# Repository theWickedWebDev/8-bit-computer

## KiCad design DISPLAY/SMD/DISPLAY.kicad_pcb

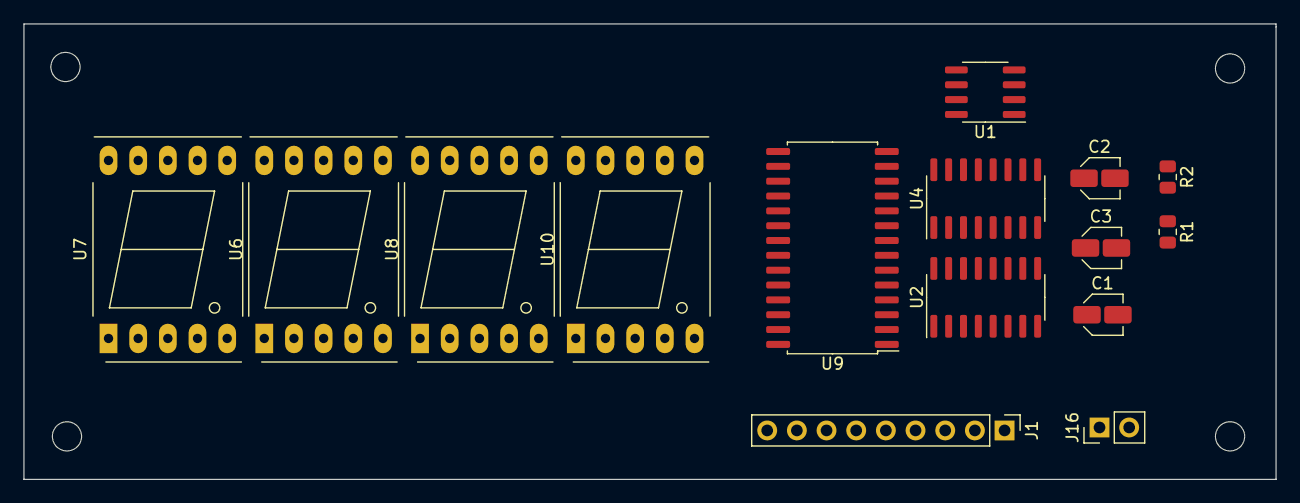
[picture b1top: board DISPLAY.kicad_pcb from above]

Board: 2 copper layers, 107.2 x 39.0 mm, 15 parts (0 on the bottom side), 28 nets, no tracks yet.

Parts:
C1, C3: CP; C_Elec_3x5.4
C2: C; C_Elec_3x5.4
J1: Conn_01x09; PinHeader_1x09_P2.54mm_Vertical
J16: Conn_01x04; PinHeader_1x02_P2.54mm_Vertical
R1, R2: R_US; R_0805_2012Metric
U1: LM555CM_NOPB; SOIC-8_3.9x4.9mm_P1.27mm
U2: 74LS76; SOIC-16_3.9x9.9mm_P1.27mm
U4: 74LS139; SOIC-16_3.9x9.9mm_P1.27mm
U6, U7, U8, U10: HDSP-7503; 7SegmentLED_LTS6760_LTS6780
U9: AT28C256; SOIC-28W_7.5x17.9mm_P1.27mm

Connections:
/A: U6.10, U7.10, U8.10, U9.11, U10.10
/B: U6.9, U7.9, U8.9, U9.12, U10.9
/C: U6.8, U7.8, U8.8, U9.13, U10.8
/CLOCK_DISPLAY: U1.3, U2.12
/D: U6.5, U7.5, U8.5, U9.15, U10.5
/DP: U6.7, U7.7, U8.7, U10.7
/E: U6.4, U7.4, U8.4, U9.16, U10.4
/F: U6.2, U7.2, U8.2, U9.17, U10.2
/G: U6.3, U7.3, U8.3, U9.18, U10.3
GND: C1.1, C2.2, C3.2, J16.2, U1.1, U2.8, U4.3, U4.4, U4.5, U4.8, U9.14, U9.20, U9.22
unnamed: C1.2, R1.2, U1.2, U1.6
unnamed: C2.1, U1.5
unnamed: J1.1, U9.10
unnamed: J1.2, U9.9
unnamed: J1.3, U9.8
unnamed: J1.4, U9.7
unnamed: J1.5, U9.6
unnamed: J1.6, U9.5
unnamed: J1.7, U9.4
unnamed: J1.8, U9.3
unnamed: J1.9, U9.25
unnamed: R1.1, R2.1, U1.7
unnamed: U2.4, U2.9, U4.1, U9.24
unnamed: U4.12, U6.1, U6.6
unnamed: U4.13, U7.1, U7.6
unnamed: U4.14, U8.1, U8.6
unnamed: U4.15, U10.1, U10.6
VCC: C3.1, J16.1, R2.2, U1.8, U2.1, U2.2, U2.3, U2.5, U2.6, U2.11, U2.13, U2.14, U2.15, U2.16, U4.2, U4.6, U4.16, U9.21, U9.27, U9.28

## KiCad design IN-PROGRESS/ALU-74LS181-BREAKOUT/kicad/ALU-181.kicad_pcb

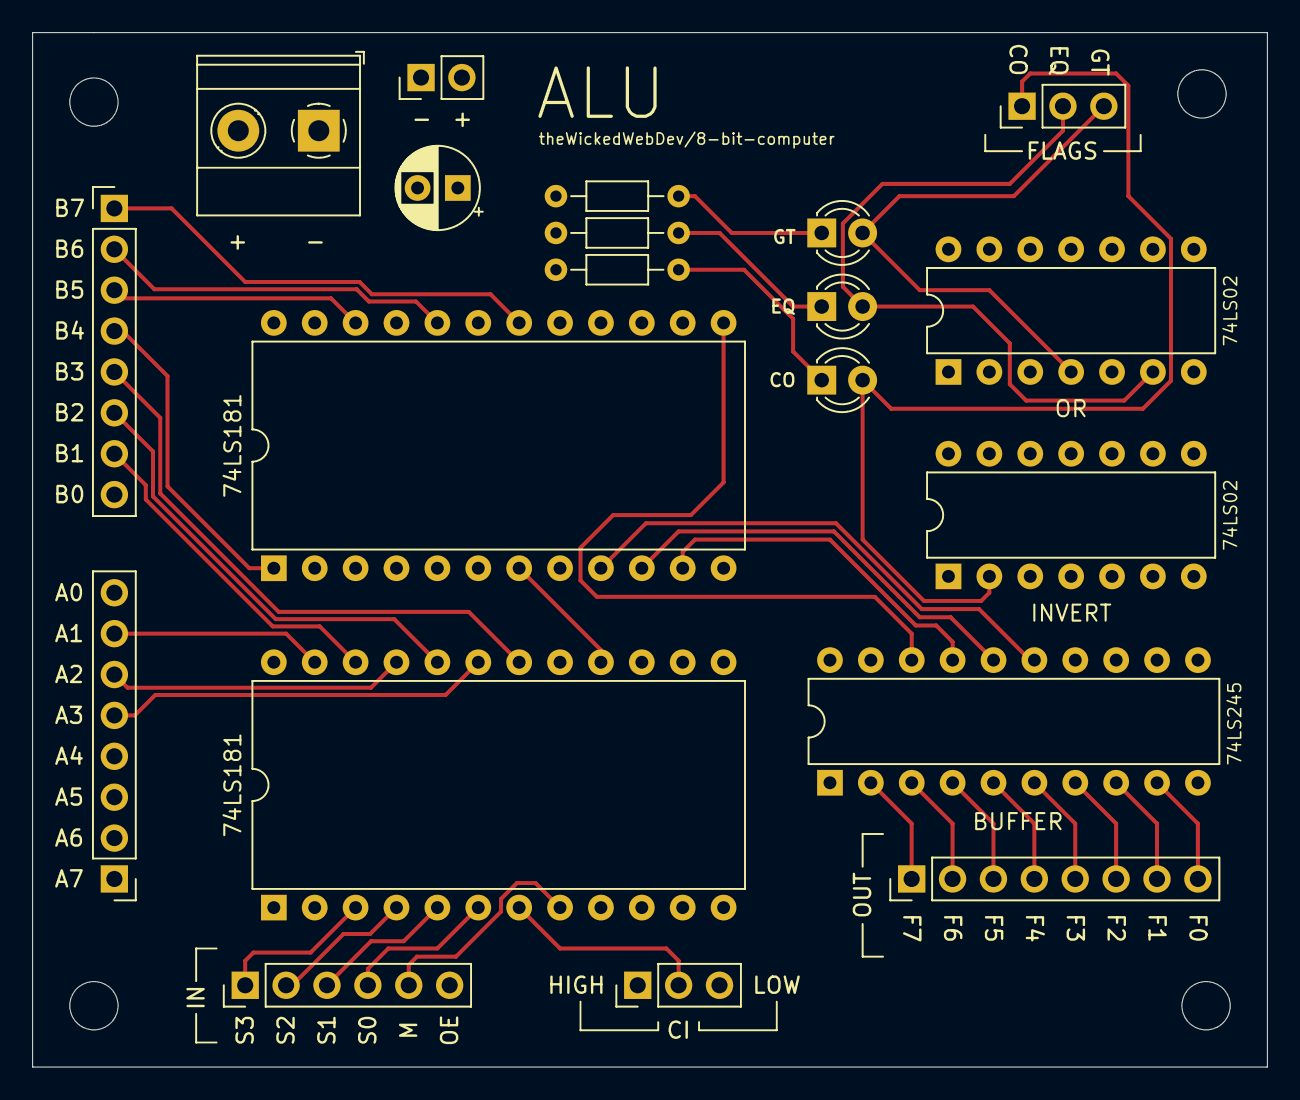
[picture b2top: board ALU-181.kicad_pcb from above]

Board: 4 copper layers, 76.7 x 64.3 mm, 20 parts (0 on the bottom side), 49 nets.

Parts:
C1: CP1_Small; CP_Radial_D5.0mm_P2.50mm
D1, D3, D4: LED; LED_D3.0mm
J1: Conn_01x02; PinHeader_1x02_P2.54mm_Vertical
J2: Screw_Terminal_01x02; TerminalBlock_Phoenix_MKDS-1,5-2_1x02_P5.00mm_Horizontal
J3, J4, J5: Conn_01x08; PinHeader_1x08_P2.54mm_Vertical
J6: Conn_01x06; PinHeader_1x06_P2.54mm_Vertical
J7, J8: Conn_01x03; PinHeader_1x03_P2.54mm_Vertical
R1, R3, R4: R_Small_US; R_Axial_DIN0204_L3.6mm_D1.6mm_P7.62mm_Horizontal
U1, U2: 74LS181; DIP-24_W15.24mm
U3: 74LS02; DIP-14_W7.62mm
U4: 74LS04; DIP-14_W7.62mm
U5: 74LS245; DIP-20_W7.62mm

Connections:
/A0: J4.8, U2.2
/A1: J4.7, U2.23
/A2: J4.6, U2.21
/A3: J4.5, U2.19
/A4: J4.4, U1.2
/A5: J4.3, U1.23
/A6: J4.2, U1.21
/A7: J4.1, U1.19
/A==B: D3.2, J7.2, U1.14, U2.14, U3.6
/A>B: D1.2, J7.3, U3.4
/B0: J5.8, U2.1
/B1: J5.7, U2.22
/B2: J5.6, U2.20
/B3: J5.5, U2.18
/B4: J5.4, U1.1
/B5: J5.3, U1.22
/B6: J5.2, U1.20
/B7: J5.1, U1.18
/CARRY: D4.2, J7.1, U4.2
/F0: J3.8, U5.9
/F1: J3.7, U5.8
/F2: J3.6, U5.7
/F3: J3.5, U5.6
/F4: J3.4, U5.5
/F5: J3.3, U5.4
/F6: J3.2, U5.3
/F7: J3.1, U5.2
/MODE: J6.5, U1.8, U2.8
/OE: J6.6, U5.19
/S0: J6.4, U1.6, U2.6
/S1: J6.3, U1.5, U2.5
/S2: J6.2, U1.4, U2.4
/S3: J6.1, U1.3, U2.3
GND: C1.2, J1.1, J2.1, J8.3, R1.2, R3.2, R4.2, U1.12, U2.12, U3.7, U4.7, U5.1, U5.10
unnamed: D1.1, R1.1
unnamed: D3.1, R3.1
unnamed: D4.1, R4.1
unnamed: J8.2, U2.7
unnamed: U1.7, U2.16
unnamed: U1.9, U5.15
unnamed: U1.10, U5.16
unnamed: U1.11, U5.17
unnamed: U1.13, U5.18
unnamed: U1.16, U3.5, U4.1
unnamed: U2.9, U5.11
unnamed: U2.10, U5.12
unnamed: U2.11, U5.13
unnamed: U2.13, U5.14
VCC: C1.1, J1.2, J2.2, J8.1, U1.24, U2.24, U3.14, U4.14, U5.20

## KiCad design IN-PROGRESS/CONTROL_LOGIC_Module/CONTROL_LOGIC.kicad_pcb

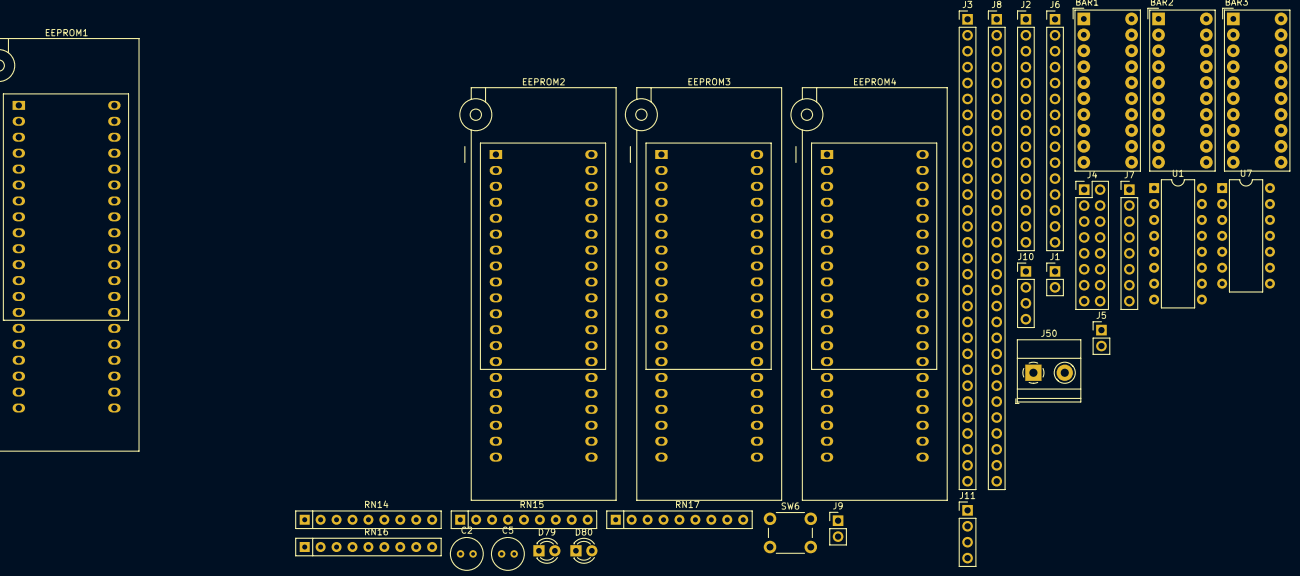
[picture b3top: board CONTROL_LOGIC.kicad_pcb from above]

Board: 2 copper layers, 30 parts (0 on the bottom side), 92 nets, no tracks yet.

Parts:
BAR1, BAR2, BAR3: HDSP-4850_2; HDSP-4850
C2, C5: CP_Small; C_Radial_D5.0mm_H7.0mm_P2.00mm
D79, D80: LED; LED_D3.0mm
EEPROM1, EEPROM2, EEPROM3, EEPROM4: AT28C256; DIP_Socket-40_W11.9_W12.7_W15.24_W17.78_W18.5_3M_240-1280-0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
J1, J5, J9: Conn_01x02; PinHeader_1x02_P2.54mm_Vertical
J2, J6: Conn_01x15; PinHeader_1x15_P2.54mm_Vertical
J3, J8: Conn_01x10; PinHeader_1x30_P2.54mm_Vertical
J4: Conn_2x08; PinHeader_2x08_P2.54mm_Vertical
J7: Conn_1x08; PinHeader_1x08_P2.54mm_Vertical
J10, J11: Conn_1x04; PinHeader_1x04_P2.54mm_Vertical
J50: Screw_Terminal_01x02; TerminalBlock_Phoenix_MKDS-1,5-2_1x02_P5.00mm_Horizontal
RN14, RN15, RN16, RN17: R_Network08_US; R_Array_SIP9
SW6: SW_Push; SW_PUSH_6mm
U1: 74LS161; DIP-16_W7.62mm
U7: 74LS04; DIP-14_W7.62mm

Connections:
/D16: BAR2.5, EEPROM2.19, J3.15, J8.15
/FLAG1: EEPROM1.7, EEPROM2.7, EEPROM3.7, EEPROM4.7, J2.4, J6.4
/FLAG2: EEPROM1.6, EEPROM2.6, EEPROM3.6, EEPROM4.6, J2.5, J6.5
/FLAG3: EEPROM1.5, EEPROM2.5, EEPROM3.5, EEPROM4.5, J2.6, J6.6
/FLAG4: EEPROM1.4, EEPROM2.4, EEPROM3.4, EEPROM4.4, J2.7, J6.7
/INST1: EEPROM1.3, EEPROM2.3, EEPROM3.3, EEPROM4.3, J2.8, J6.8
/INST2: EEPROM1.25, EEPROM2.25, EEPROM3.25, EEPROM4.25, J2.9, J6.9
/INST3: EEPROM1.24, EEPROM2.24, EEPROM3.24, EEPROM4.24, J2.10, J6.10
/INST4: EEPROM1.21, EEPROM2.21, EEPROM3.21, EEPROM4.21, J2.11, J6.11
/INST5: EEPROM1.23, EEPROM2.23, EEPROM3.23, EEPROM4.23, J2.12, J6.12
/INST6: EEPROM1.2, EEPROM2.2, EEPROM3.2, EEPROM4.2, J2.13, J6.13
/INST7: EEPROM1.26, EEPROM2.26, EEPROM3.26, EEPROM4.26, J2.14, J6.14
/INST8: EEPROM1.1, EEPROM2.1, EEPROM3.1, EEPROM4.1, J2.15, J6.15
/STEP1: EEPROM1.10, EEPROM2.10, EEPROM3.10, EEPROM4.10, J2.1, J6.1, U1.14
/STEP2: EEPROM1.9, EEPROM2.9, EEPROM3.9, EEPROM4.9, J2.2, J6.2, U1.13
/STEP3: EEPROM1.8, EEPROM2.8, EEPROM3.8, EEPROM4.8, J2.3, J6.3, U1.12
/μ1: BAR1.10, EEPROM1.11, J3.30, J8.30
/μ2: BAR1.9, EEPROM1.12, J3.29, J8.29
/μ3: BAR1.8, EEPROM1.13, J3.28, J8.28
/μ4: BAR1.7, EEPROM1.15, J3.27, J8.27
/μ5: BAR1.6, EEPROM1.16, J3.26, J8.26
/μ6: BAR1.5, EEPROM1.17, J3.25, J8.25
/μ7: BAR1.4, EEPROM1.18, J3.24, J8.24
/μ8: BAR1.3, EEPROM1.19, J3.23, J8.23
/μ9: BAR1.2, EEPROM2.11, J3.22, J8.22
/μ10: BAR1.1, EEPROM2.12, J3.21, J8.21
/μ11: BAR2.10, EEPROM2.13, J3.20, J8.20
/μ12: BAR2.9, EEPROM2.15, J3.19, J8.19
/μ13: BAR2.8, EEPROM2.16, J3.18, J8.18
/μ14: BAR2.7, EEPROM2.17, J3.17, J8.17
/μ15: BAR2.6, EEPROM2.18, J3.16, J8.16
/μ17: BAR2.4, EEPROM3.11, J3.14, J8.14
/μ18: BAR2.3, EEPROM3.12, J3.13, J8.13
/μ19: BAR2.2, EEPROM3.13, J3.12, J8.12
/μ20: BAR2.1, EEPROM3.15, J3.11, J8.11
/μ21: BAR3.10, EEPROM3.16, J3.10, J8.10
/μ22: BAR3.9, EEPROM3.17, J3.9, J8.9
/μ23: BAR3.8, EEPROM3.18, J3.8, J8.8
/μ24: BAR3.7, EEPROM3.19, J3.7, J8.7
/μ25: BAR3.6, EEPROM4.11, J3.6, J8.6
/μ26: BAR3.5, EEPROM4.12, J3.5, J8.5
/μ27: BAR3.4, EEPROM4.13, J3.4, J8.4
/μ28: BAR3.3, EEPROM4.15, J3.3, J8.3
/μ29: BAR3.2, EEPROM4.16, J3.2, J8.2
/μ30: BAR3.1, EEPROM4.17, J3.1, J8.1
/μ31: D79.2, EEPROM4.18, J9.2
/μ32: D80.2, EEPROM4.19, J4.1, J4.2, J4.3, J4.4, J4.5, J4.6, J4.7, J4.8, J7.5, J7.6, J7.7, J7.8, J9.1, SW6.1, U7.1
CLOCK: U1.2, U7.12
GND: C2.2, C5.2, EEPROM1.14, EEPROM1.20, EEPROM1.22, EEPROM2.14, EEPROM2.20, EEPROM2.22, EEPROM3.14, EEPROM3.20, EEPROM3.22, EEPROM4.14, EEPROM4.20, EEPROM4.22, J1.1, J50.2, RN14.1, RN15.1, RN16.1, RN17.1, U1.7, U1.8, U1.10, U7.7
unnamed: BAR1.11, RN14.9
unnamed: BAR1.12, RN14.8
unnamed: BAR1.13, RN14.7
unnamed: BAR1.14, RN14.6
unnamed: BAR1.15, RN14.5
unnamed: BAR1.16, RN14.4
unnamed: BAR1.17, RN14.3
unnamed: BAR1.18, RN14.2
unnamed: BAR1.19, RN15.9
unnamed: BAR1.20, RN15.8
unnamed: BAR2.11, RN15.7
unnamed: BAR2.12, RN15.6
unnamed: BAR2.13, RN15.5
unnamed: BAR2.14, RN15.4
unnamed: BAR2.15, RN15.3
unnamed: BAR2.16, RN15.2
unnamed: BAR2.17, RN16.9
unnamed: BAR2.18, RN16.8
unnamed: BAR2.19, RN16.7
unnamed: BAR2.20, RN16.6
unnamed: BAR3.11, RN16.5
unnamed: BAR3.12, RN16.4
unnamed: BAR3.13, RN16.3
unnamed: BAR3.14, RN16.2
unnamed: BAR3.15, RN17.9
unnamed: BAR3.16, RN17.8
unnamed: BAR3.17, RN17.7
unnamed: BAR3.18, RN17.6
unnamed: BAR3.19, RN17.5
unnamed: BAR3.20, RN17.4
unnamed: D79.1, RN17.3
unnamed: D80.1, RN17.2
unnamed: J4.9, J4.10, J4.11, J4.12, J4.13, J4.14, J4.15, J4.16, J7.1, J7.2, J7.3, J7.4, U7.2
unnamed: J5.1, J5.2, U7.13
unnamed: J10.1, U7.11
unnamed: J10.2, U7.9
unnamed: J10.3, U7.5
unnamed: J10.4, U7.3
unnamed: J11.1, U7.4
unnamed: J11.2, U7.6
unnamed: J11.3, U7.8
unnamed: J11.4, U7.10
VCC: C2.1, C5.1, EEPROM1.27, EEPROM1.28, EEPROM2.27, EEPROM2.28, EEPROM3.27, EEPROM3.28, EEPROM4.27, EEPROM4.28, J1.2, SW6.2, U1.9, U1.16, U7.14

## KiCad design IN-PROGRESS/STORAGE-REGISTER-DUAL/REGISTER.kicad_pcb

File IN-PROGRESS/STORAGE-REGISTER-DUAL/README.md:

# 2x 8-bit Registers

This module contains two 8bit registers using the `74LS173` chip ([datasheet](https://www.jameco.com/Jameco/Products/ProdDS/46922.pdf)).

The output is buffered behind an octal tri-state bus transceiver chip using the `74LS245` ([datasheet](https://www.futurlec.com/74LS/74LS245pr.shtml))

### ✅ Tested this module and verified it works as expected

<br/>

## Pinout

| AI 	| AO 	| RS1 	| BI	| BO 	| RS2 	| CLK            | OUTPUT                            |
|----	|----	|----	|----	|----	|----	|----            |----                               |
|  LOW 	|  x	|  LOW  |  x 	|   x  	| x     |  RISING EDGE   | Latch data to A register from Bus |
|  x 	|  LOW	|  LOW	|  x 	|   x  	| x     |  RISING EDGE   | Output A register to Bus          |
|  x 	|  x	|  x    |  LOW 	|   x  	| LOW   |  RISING EDGE   | Latch data to B register from Bus |
|  x 	|  x	|  x	|  x 	|   LOW	| LOW   |  RISING EDGE   | Output B register to Bus          |
|  x 	|  x	|  HIGH	|  x 	|   x	| x     |  x             | Reset A Register                  |
|  x 	|  x	|  x	|  x 	|   x	| HIGH  |  x             | Reset B Register                  |

<br/>

## Breadboard

Made with Fritzing

(1 of the 2 registers in this module)

<br/>

## Schematic

Made with Kicad

<br/>

## PCB
Made with Kicad and fabricated with [JLCPCB](https://jlcpcb.com/)

Actual cost for me to fabricate this board.

| Fab 	    | S&H 	    | Total     |
|----	    |----	    |----       |
|  $9.50	|  $12.80 	|  $22.30   |

<br/>

<br/>

## Gerber View (SVG)

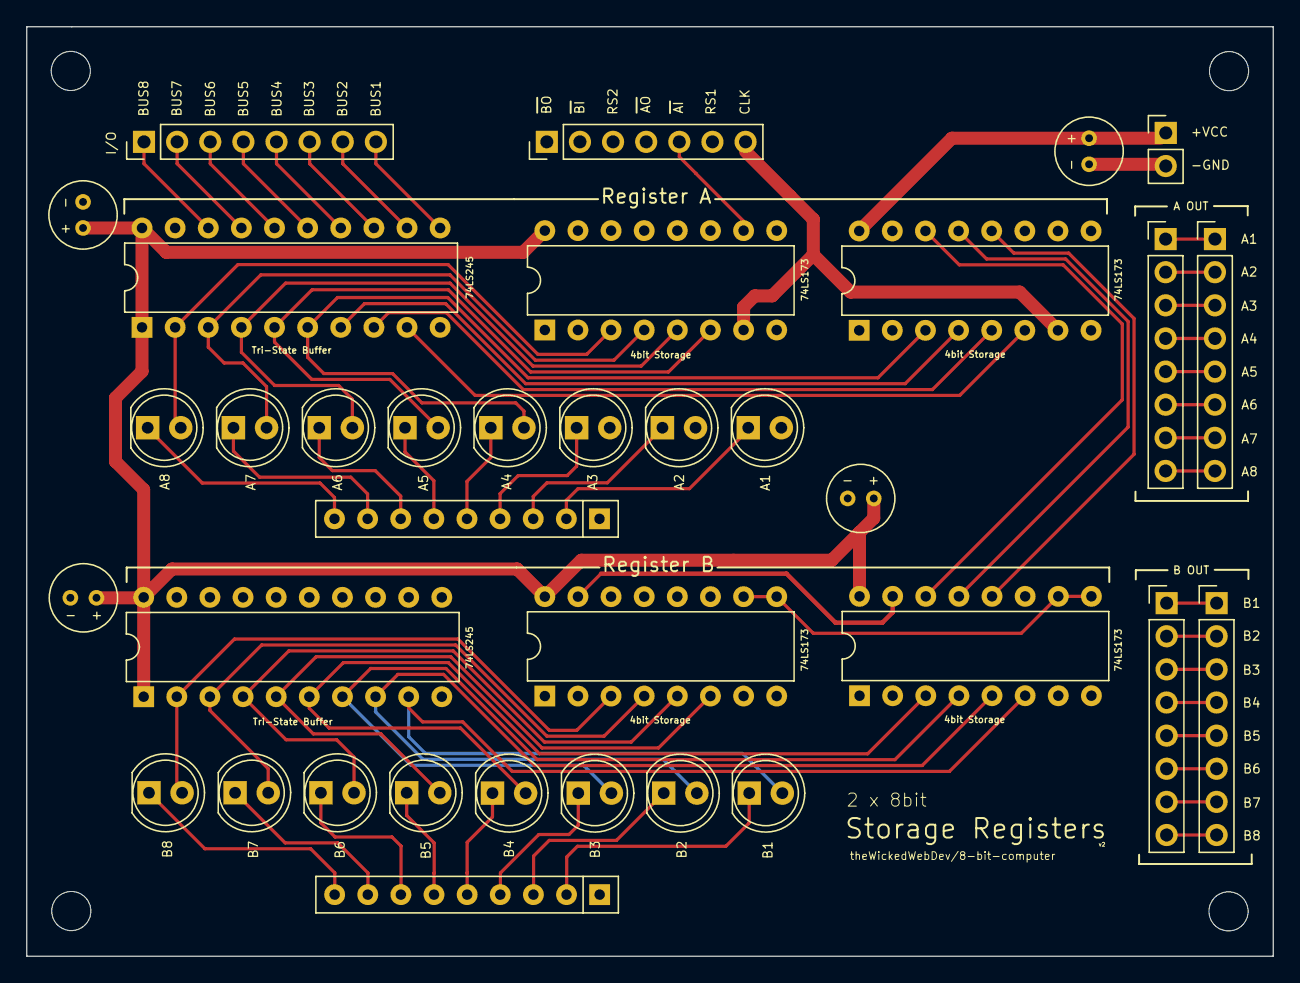
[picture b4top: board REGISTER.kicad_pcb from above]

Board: 4 copper layers, 95.6 x 71.3 mm, 35 parts (0 on the bottom side), 49 nets.

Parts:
C1, C2, C3, C4: CP1; C_Radial_D5.0mm_H7.0mm_P2.00mm
D1, D2, D3, D4, D5, D6, D7, D8, D9, D10, D11, D12, D13, D14, D15, D16: LED; LED_D5.0mm
J1, J2, J5, J7, J8: Conn_01x08; PinHeader_1x08_P2.54mm_Vertical
J3: Conn_01x02; PinHeader_1x02_P2.54mm_Vertical
J6: Conn_01x07; PinHeader_1x07_P2.54mm_Vertical
RN1, RN2: R_Network08; R_Array_SIP9
U1, U4: 74LS245; DIP-20_W7.62mm
U2, U3, U5, U6: 74LS173; DIP-16_W7.62mm

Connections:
/A1: D8.2, J7.1, J8.1, U1.9, U3.6
/A2: D7.2, J7.2, J8.2, U1.8, U3.5
/A3: D6.2, J7.3, J8.3, U1.7, U3.4
/A4: D5.2, J7.4, J8.4, U1.6, U3.3
/A5: D4.2, J7.5, J8.5, U1.5, U2.6
/A6: D3.2, J7.6, J8.6, U1.4, U2.5
/A7: D2.2, J7.7, J8.7, U1.3, U2.4
/A8: D1.2, J7.8, J8.8, U1.2, U2.3
/AI: J6.5, U2.9, U2.10, U3.9, U3.10
/AO: J6.4, U1.19
/B1: D16.2, J1.1, J2.1, U4.9, U6.6
/B2: D15.2, J1.2, J2.2, U4.8, U6.5
/B3: D14.2, J1.3, J2.3, U4.7, U6.4
/B4: D13.2, J1.4, J2.4, U4.6, U6.3
/B5: D12.2, J1.5, J2.5, U4.5, U5.6
/B6: D11.2, J1.6, J2.6, U4.4, U5.5
/B7: D10.2, J1.7, J2.7, U4.3, U5.4
/B8: D9.2, J1.8, J2.8, U4.2, U5.3
/BI: J6.2, U5.9, U5.10, U6.9, U6.10
/BO: J6.1, U4.19
/CLK: J6.7, U2.7, U3.7, U5.7, U6.7
/I1: J5.8, U1.11, U3.11, U4.11, U6.11
/I2: J5.7, U1.12, U3.12, U4.12, U6.12
/I3: J5.6, U1.13, U3.13, U4.13, U6.13
/I4: J5.5, U1.14, U3.14, U4.14, U6.14
/I5: J5.4, U1.15, U2.11, U4.15, U5.11
/I6: J5.3, U1.16, U2.12, U4.16, U5.12
/I7: J5.2, U1.17, U2.13, U4.17, U5.13
/I8: J5.1, U1.18, U2.14, U4.18, U5.14
/RS1: J6.6, U2.15, U3.15
/RS2: J6.3, U5.15, U6.15
GND: C1.2, C2.2, C3.2, C4.2, J3.2, RN1.1, RN2.1, U1.10, U2.1, U2.2, U2.8, U3.1, U3.2, U3.8, U4.10, U5.1, U5.2, U5.8, U6.1, U6.2, U6.8
unnamed: D1.1, RN1.9
unnamed: D2.1, RN1.8
unnamed: D3.1, RN1.7
unnamed: D4.1, RN1.6
unnamed: D5.1, RN1.5
unnamed: D6.1, RN1.4
unnamed: D7.1, RN1.3
unnamed: D8.1, RN1.2
unnamed: D9.1, RN2.9
unnamed: D10.1, RN2.8
unnamed: D11.1, RN2.7
unnamed: D12.1, RN2.6
unnamed: D13.1, RN2.5
unnamed: D14.1, RN2.4
unnamed: D15.1, RN2.3
unnamed: D16.1, RN2.2
VCC: C1.1, C2.1, C3.1, C4.1, J3.1, U1.1, U1.20, U2.16, U3.16, U4.1, U4.20, U5.16, U6.16

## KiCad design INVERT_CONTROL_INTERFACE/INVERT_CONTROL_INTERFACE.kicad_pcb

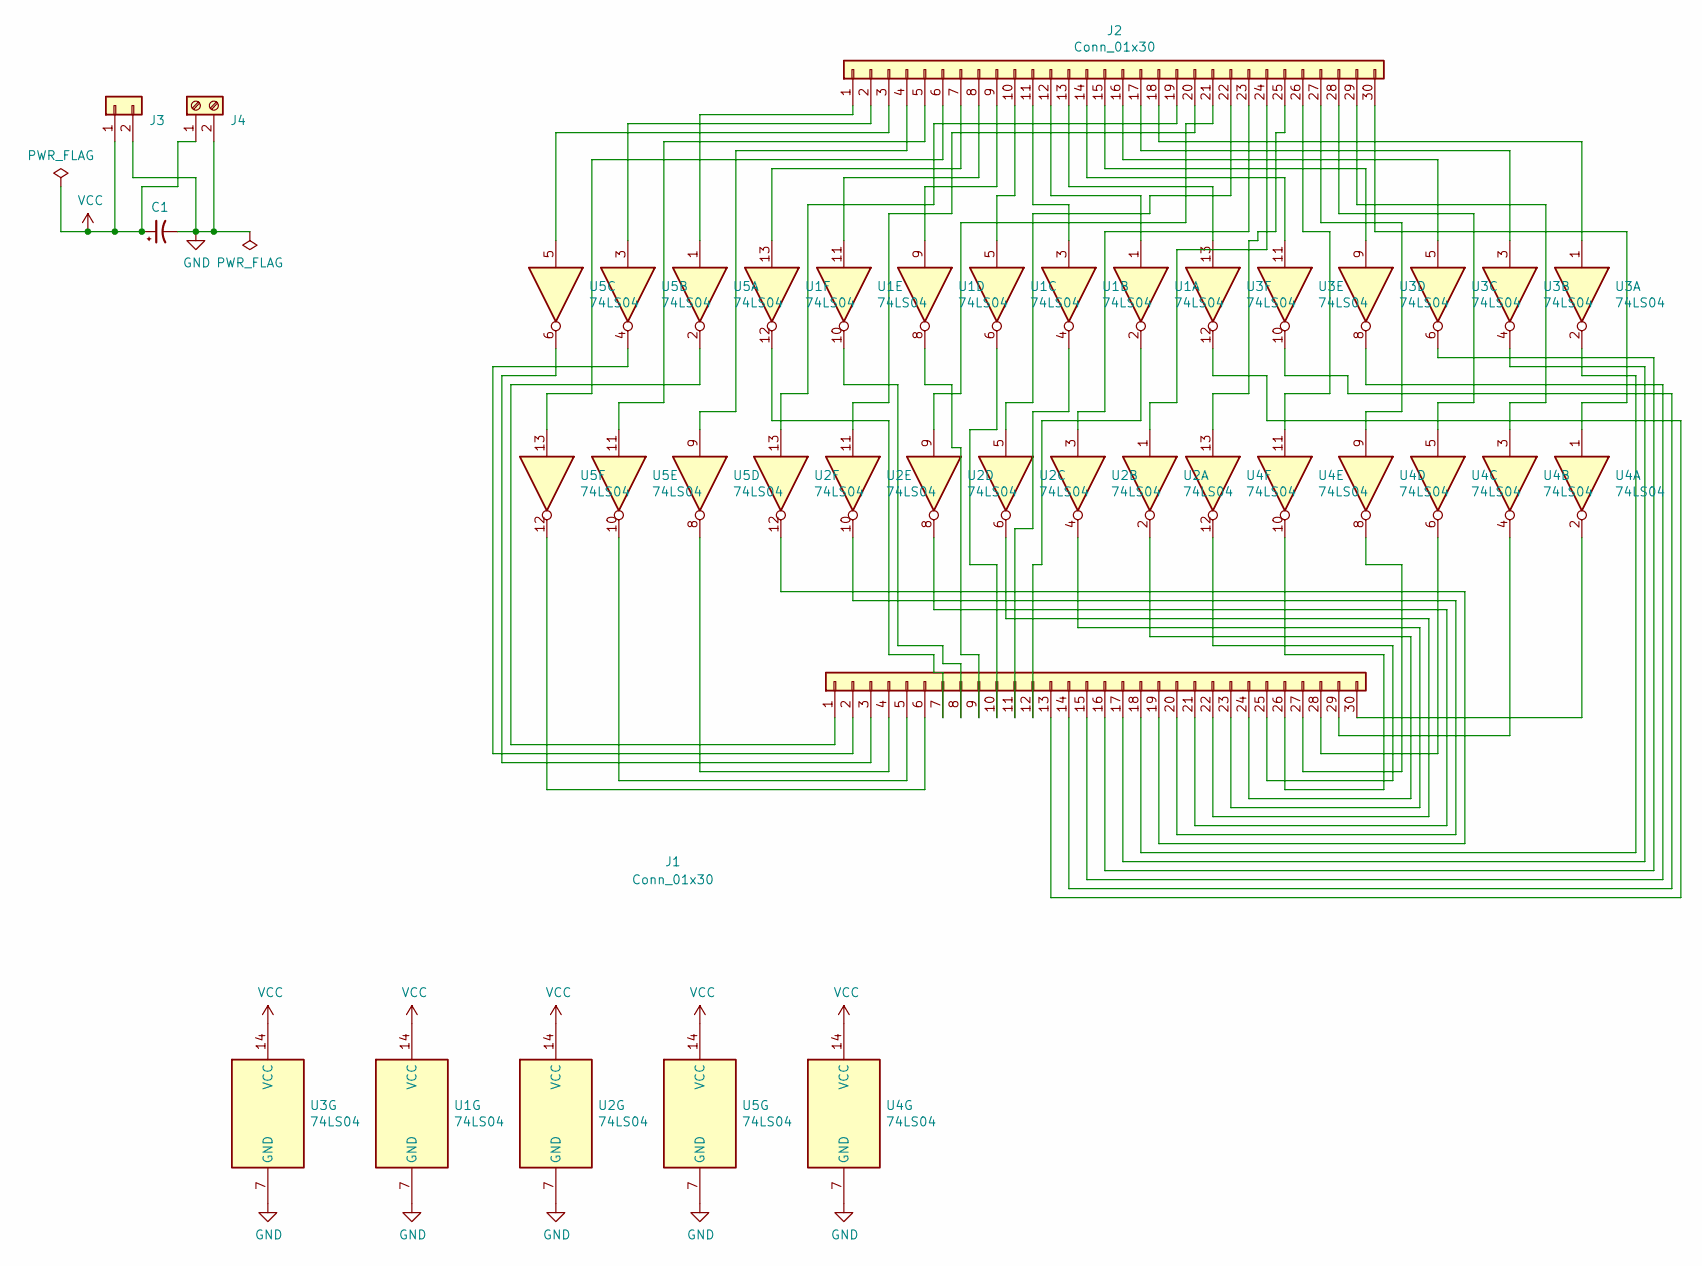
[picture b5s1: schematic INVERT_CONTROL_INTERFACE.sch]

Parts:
C1: CP1_Small; CP_Radial_D8.0mm_P3.50mm
J1, J2: Conn_01x30; PinHeader_1x30_P2.54mm_Vertical
J3: Conn_01x02; PinHeader_1x02_P2.54mm_Vertical
J4: Screw_Terminal_01x02; TerminalBlock_Phoenix_MKDS-1,5-2_1x02_P5.00mm_Horizontal
U1, U2, U3, U4, U5: 74LS04; DIP-14_W7.62mm

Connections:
GND: C1.2, J3.2, J4.2, U1.7 (GND), U2.7 (GND), U3.7 (GND), U4.7 (GND), U5.7 (GND)
unnamed: J1.1, U5.2
unnamed: J1.2, U5.4
unnamed: J1.3, U5.6
unnamed: J1.4, U5.8
unnamed: J1.5, U5.10
unnamed: J1.6, U5.12
unnamed: J1.7, U1.12
unnamed: J1.8, U1.10
unnamed: J1.9, U1.8
unnamed: J1.10, U1.6
unnamed: J1.11, U1.4
unnamed: J1.12, U1.2
unnamed: J1.13, U3.12
unnamed: J1.14, U3.10
unnamed: J1.15, U3.8
unnamed: J1.16, U3.6
unnamed: J1.17, U3.4
unnamed: J1.18, U3.2
unnamed: J1.19, U2.12
unnamed: J1.20, U2.10
unnamed: J1.21, U2.8
unnamed: J1.22, U2.6
unnamed: J1.23, U2.4
unnamed: J1.24, U2.2
unnamed: J1.25, U4.12
unnamed: J1.26, U4.10
unnamed: J1.27, U4.8
unnamed: J1.28, U4.6
unnamed: J1.29, U4.4
unnamed: J1.30, U4.2
unnamed: J2.1, U5.1
unnamed: J2.2, U5.3
unnamed: J2.3, U5.5
unnamed: J2.4, U5.9
unnamed: J2.5, U5.11
unnamed: J2.6, U5.13
unnamed: J2.7, U1.13
unnamed: J2.8, U1.11
unnamed: J2.9, U1.9
unnamed: J2.10, U1.5
unnamed: J2.11, U1.3
unnamed: J2.12, U1.1
unnamed: J2.13, U3.13
unnamed: J2.14, U3.11
unnamed: J2.15, U3.9
unnamed: J2.16, U3.5
unnamed: J2.17, U3.3
unnamed: J2.18, U3.1
unnamed: J2.19, U2.13
unnamed: J2.20, U2.11
unnamed: J2.21, U2.9
unnamed: J2.22, U2.5
unnamed: J2.23, U2.3
unnamed: J2.24, U2.1
unnamed: J2.25, U4.13
unnamed: J2.26, U4.11
unnamed: J2.27, U4.9
unnamed: J2.28, U4.5
unnamed: J2.29, U4.3
unnamed: J2.30, U4.1
VCC: C1.1, J3.1, J4.1, U1.14 (VCC), U2.14 (VCC), U3.14 (VCC), U4.14 (VCC), U5.14 (VCC)

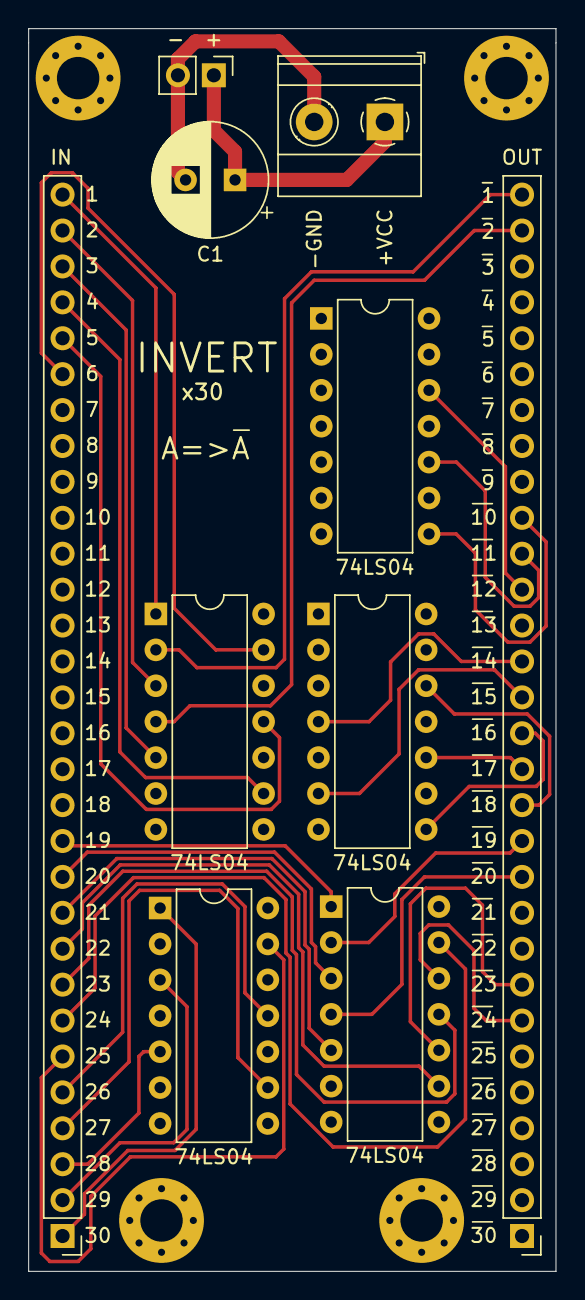
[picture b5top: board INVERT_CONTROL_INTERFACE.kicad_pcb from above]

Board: 4 copper layers, 37.3 x 87.9 mm, 10 parts (0 on the bottom side), 62 nets.

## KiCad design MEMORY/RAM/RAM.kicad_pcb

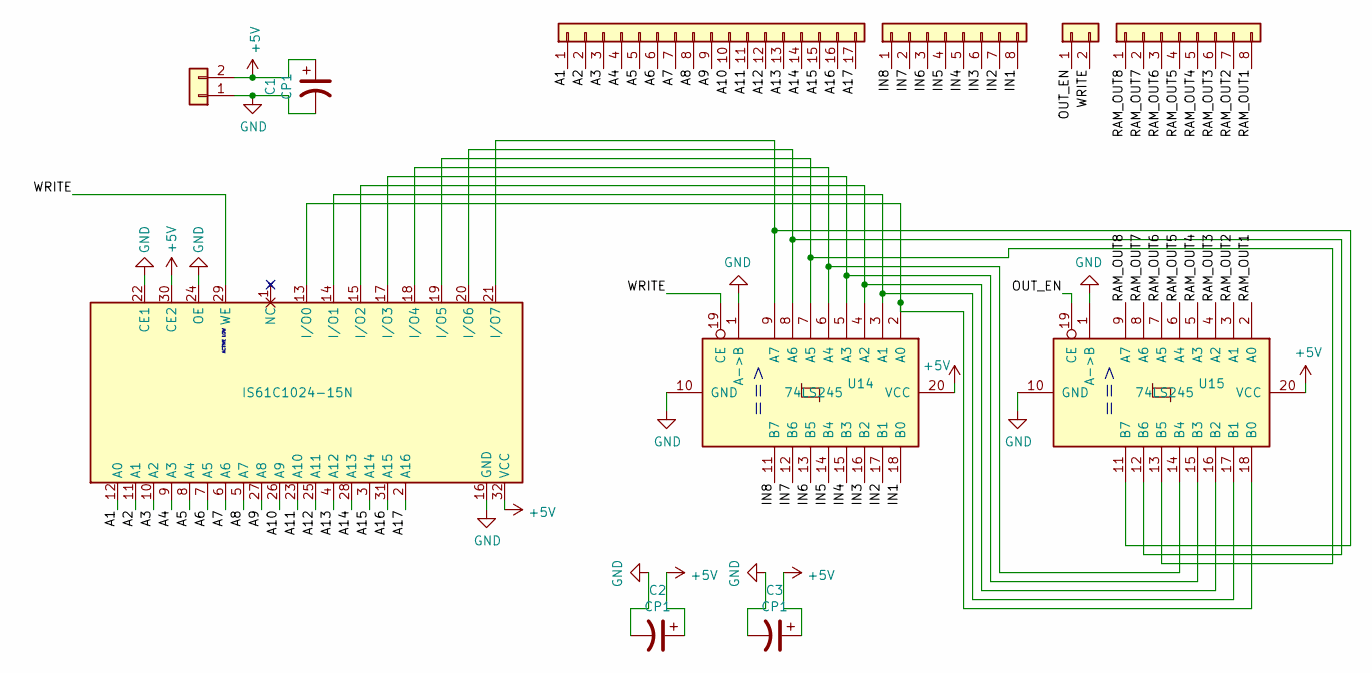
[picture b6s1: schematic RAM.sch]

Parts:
C1, C2, C3: CP1; C_Radial_D4.0mm_H5.0mm_P1.50mm
J1, J4: Conn_01x02; PinHeader_1x02_P2.54mm_Vertical
J2: Conn_01x017; PinHeader_1x17_P2.54mm_Vertical
J3, J5: Conn_01x08; PinHeader_1x08_P2.54mm_Vertical
U6: IS61C1024-15N; DIP-32_W7.62mm
U14, U15: 74LS245; DIP-20_W7.62mm

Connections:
+5V: C1.1, C2.1, C3.1, J1.2, U6.30 (CE2), U6.32 (VCC), U14.20 (VCC), U15.20 (VCC)
/A1: J2.1, U6.12 (A0)
/A2: J2.2, U6.11 (A1)
/A3: J2.3, U6.10 (A2)
/A4: J2.4, U6.9 (A3)
/A5: J2.5, U6.8 (A4)
/A6: J2.6, U6.7 (A5)
/A7: J2.7, U6.6 (A6)
/A8: J2.8, U6.5 (A7)
/A9: J2.9, U6.27 (A8)
/A10: J2.10, U6.26 (A9)
/A11: J2.11, U6.23 (A10)
/A12: J2.12, U6.25 (A11)
/A13: J2.13, U6.4 (A12)
/A14: J2.14, U6.28 (A13)
/A15: J2.15, U6.3 (A14)
/A16: J2.16, U6.31 (A15)
/A17: J2.17, U6.2 (A16)
/IN1: J3.8, U14.18 (B0)
/IN2: J3.7, U14.17 (B1)
/IN3: J3.6, U14.16 (B2)
/IN4: J3.5, U14.15 (B3)
/IN5: J3.4, U14.14 (B4)
/IN6: J3.3, U14.13 (B5)
/IN7: J3.2, U14.12 (B6)
/IN8: J3.1, U14.11 (B7)
/OUT_EN: J4.1, U15.19 (CE)
/RAM_OUT1: J5.8, U15.2 (A0)
/RAM_OUT2: J5.7, U15.3 (A1)
/RAM_OUT3: J5.6, U15.4 (A2)
/RAM_OUT4: J5.5, U15.5 (A3)
/RAM_OUT5: J5.4, U15.6 (A4)
/RAM_OUT6: J5.3, U15.7 (A5)
/RAM_OUT7: J5.2, U15.8 (A6)
/RAM_OUT8: J5.1, U15.9 (A7)
/WRITE: J4.2, U6.29 (WE), U14.19 (CE)
GND: C1.2, C2.2, C3.2, J1.1, U6.16 (GND), U6.22 (CE1), U6.24 (OE), U14.1 (A->B), U14.10 (GND), U15.1 (A->B), U15.10 (GND)
unnamed: U6.13 (I/O0), U14.2 (A0), U15.18 (B0)
unnamed: U6.14 (I/O1), U14.3 (A1), U15.17 (B1)
unnamed: U6.15 (I/O2), U14.4 (A2), U15.16 (B2)
unnamed: U6.17 (I/O3), U14.5 (A3), U15.15 (B3)
unnamed: U6.18 (I/O4), U14.6 (A4), U15.14 (B4)
unnamed: U6.19 (I/O5), U14.7 (A5), U15.13 (B5)
unnamed: U6.20 (I/O6), U14.8 (A6), U15.12 (B6)
unnamed: U6.21 (I/O7), U14.9 (A7), U15.11 (B7)

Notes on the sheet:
==>
ACTIVE LOW

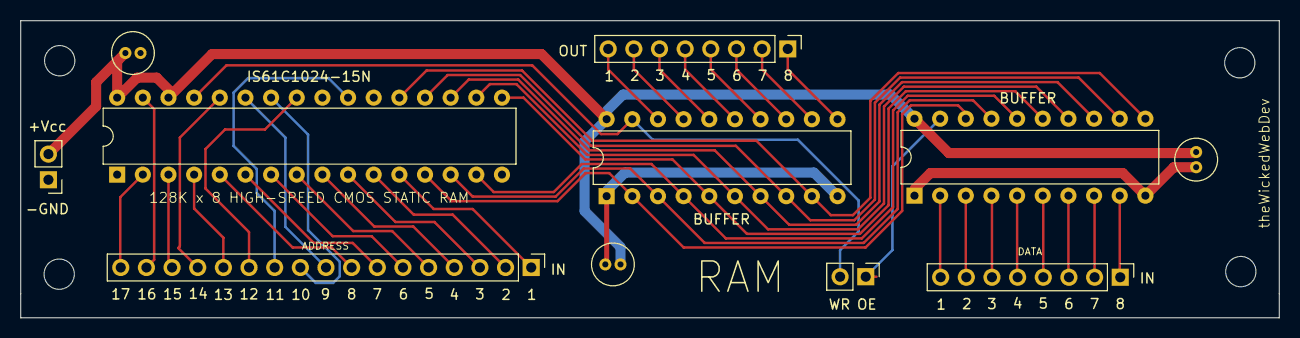
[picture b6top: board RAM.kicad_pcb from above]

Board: 2 copper layers, 124.6 x 29.4 mm, 11 parts (0 on the bottom side), 45 nets.

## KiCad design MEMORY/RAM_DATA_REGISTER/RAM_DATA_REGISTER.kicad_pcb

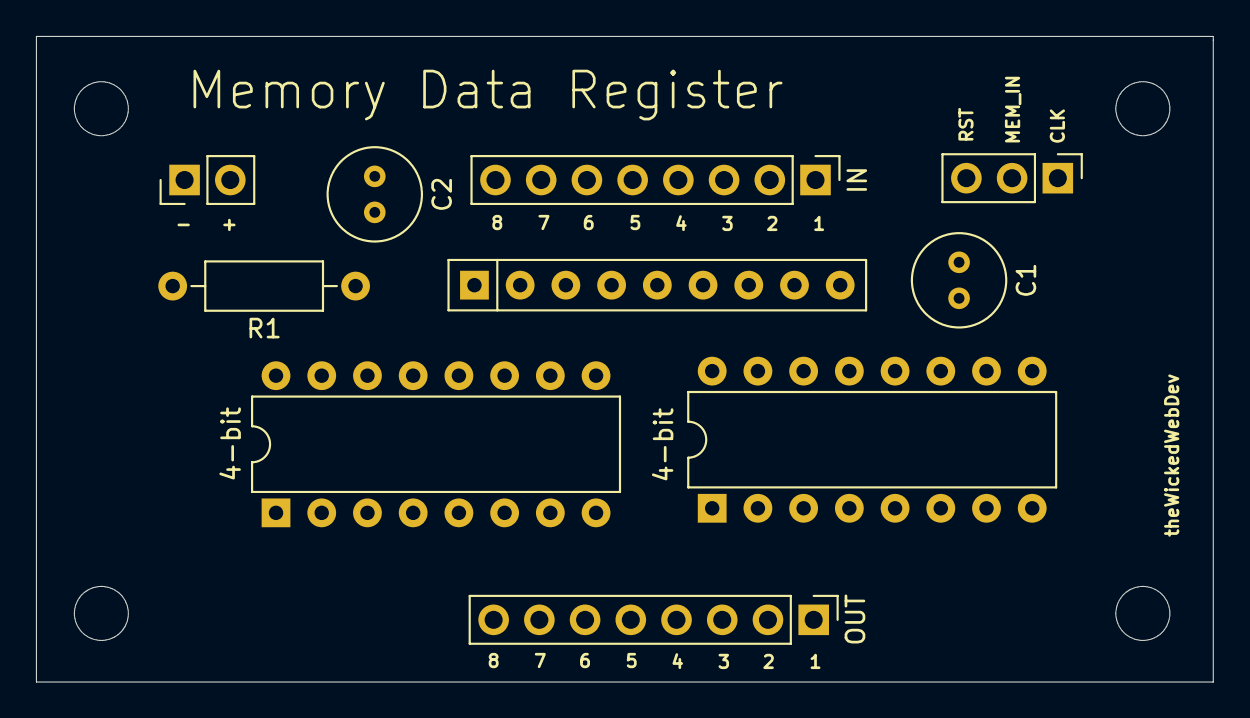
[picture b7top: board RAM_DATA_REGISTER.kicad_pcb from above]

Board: 4 copper layers, 65.4 x 35.9 mm, 10 parts (0 on the bottom side), 22 nets, no tracks yet.

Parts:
C1, C2: CP_Small; C_Radial_D5.0mm_H7.0mm_P2.00mm
IN: Conn_01x08; PinHeader_1x08_P2.54mm_Vertical
J1: Conn_01x02; PinHeader_1x02_P2.54mm_Vertical
J2: Conn_01x03; PinHeader_1x03_P2.54mm_Vertical
OUT: Conn_01x8; PinHeader_1x08_P2.54mm_Vertical
R1: R_Small_US; R_Axial_DIN0207_L6.3mm_D2.5mm_P10.16mm_Horizontal
RN1: R_Network08_US; R_Array_SIP9
U1, U2: 74LS173; DIP-16_W7.62mm

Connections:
+5V: U1.16, U2.16
/ADR1: OUT.1, U2.6
/ADR2: OUT.2, U2.5
/ADR3: OUT.3, U2.4
/ADR4: OUT.4, U2.3
/ADR5: OUT.5, U1.6
/ADR6: OUT.6, U1.5
/ADR7: OUT.7, U1.4
/ADR8: OUT.8, U1.3
/CLOCK: J2.1, U1.7, U2.7
/D1: IN.1, RN1.9, U2.11
/D2: IN.2, RN1.8, U2.12
/D3: IN.3, RN1.7, U2.13
/D4: IN.4, RN1.6, U2.14
/D5: IN.5, RN1.5, U1.11
/D6: IN.6, RN1.4, U1.12
/D7: IN.7, RN1.3, U1.13
/D8: IN.8, RN1.2, U1.14
/MEM_IN: J2.2, U1.9, U1.10, U2.9, U2.10
/RST: J2.3, R1.1, U1.15, U2.15
GND: C1.2, C2.2, J1.1, R1.2, RN1.1, U1.1, U1.2, U1.8, U2.1, U2.2, U2.8
VCC: C1.1, C2.1, J1.2
